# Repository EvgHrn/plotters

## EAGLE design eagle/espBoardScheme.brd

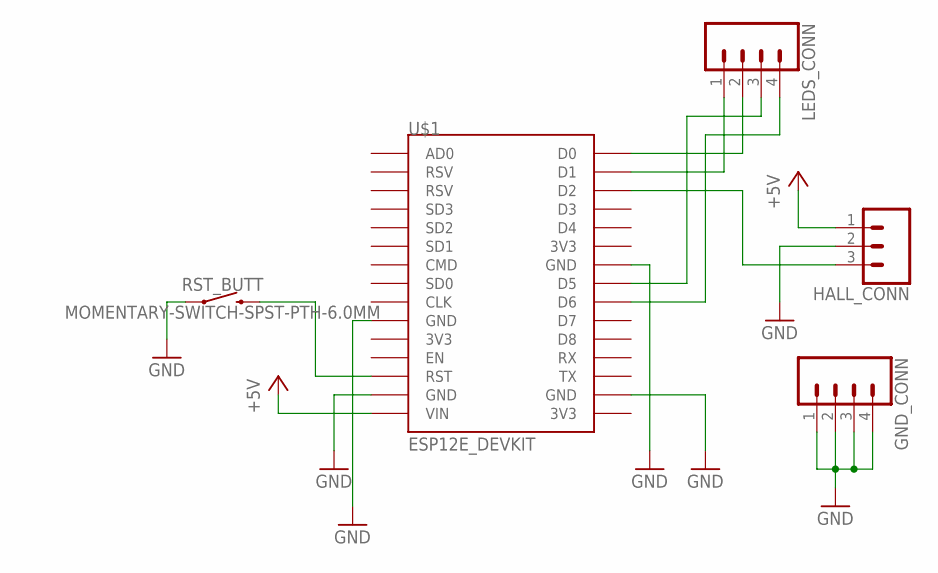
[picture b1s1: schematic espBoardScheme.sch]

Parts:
GND_CONN: CONN_04; 1X04
HALL_CONN: CONN_03; 1X03
LEDS_CONN: CONN_04; 1X04
RST_BUTT: MOMENTARY-SWITCH-SPST-PTH-6.0MM; TACTILE_SWITCH_PTH_6.0MM
U$1: ESP12E_DEVKIT

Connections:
+5V: HALL_CONN.1, U$1.VIN
GND: GND_CONN.1, GND_CONN.2, GND_CONN.3, GND_CONN.4, HALL_CONN.2, RST_BUTT.1, U$1.GND@0 (GND), U$1.GND@1 (GND), U$1.GND@2 (GND), U$1.GND@3 (GND)
unnamed: HALL_CONN.3, U$1.D2
unnamed: RST_BUTT.3 (2), U$1.RST
unnamed: LEDS_CONN.2, U$1.D0
unnamed: LEDS_CONN.1, U$1.D1
unnamed: LEDS_CONN.3, U$1.D5
unnamed: LEDS_CONN.4, U$1.D6

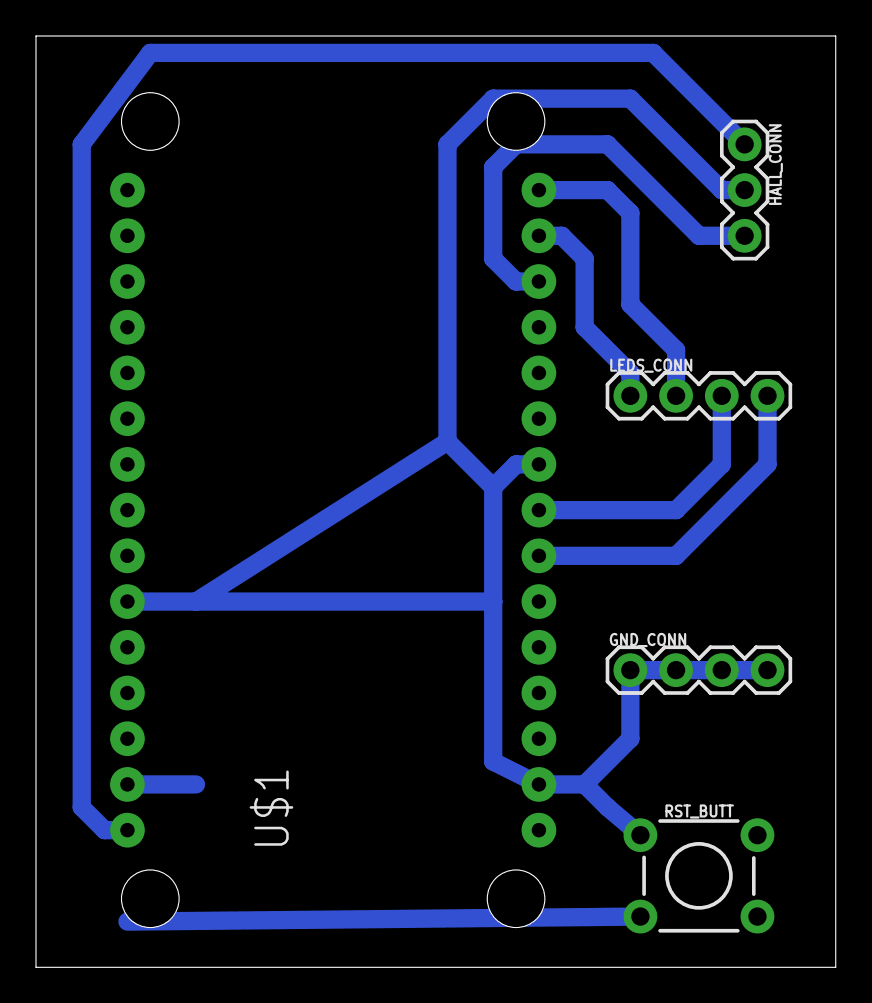
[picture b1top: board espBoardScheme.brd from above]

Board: 2 copper layers, 44.4 x 51.7 mm, 5 parts (0 on the bottom side), 8 nets.

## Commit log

2017-03-27 Init
2017-03-27 Add slim/pdo package
2017-03-27 Install slim/twig-view package
2017-03-27 Register twig on container
2017-03-27 Add first main root
2017-03-28 Some frontend
2017-03-28 Add simple google chart
2017-03-28 Add period select to form
2017-03-28 Add getting data for chart from json
2017-03-29 Add simple route for post
2017-03-29 Add db class skeleton
2017-03-29 Add saving GET data to database
2017-03-29 Edit .htaccess
2017-03-29 Start function to get data from db
2017-03-29 Add pwd fo db access
2017-03-30 dfsdf
2017-03-30 Add carbon package
2017-03-30 Start create DatesWorker
2017-03-31 Contin with DatesWorker
2017-03-31 Db getData sum meters for any period
2017-03-31 Add parcelWeeks to DatesWorker
2017-03-31 Add test for parcelDays
2017-03-31 Start add test for ParcelWeeks
2017-04-01 Fix bug in parcelDays
2017-04-01 Add testParcelMonths
2017-04-01 Add parcelMonths
2017-04-01 Add comments to parcelMonths
2017-04-01 Add testParcelYears
2017-04-01 Add parcelYears
2017-04-01 Add doc blocks to DatesWorker's methods
2017-04-01 Add doc blocks to Db class methods
2017-04-01 Make css and js local
2017-04-01 Fix some bugs
2017-04-01 Finish chart
2017-04-01 Add data.json for chart to gitignore
2017-04-01 Fix bug with time from form
2017-04-01 Add cookies for form
2017-04-05 Rename Db.php
2017-04-05 Rename DatesWorker.php
2017-04-05 Add try catch for writig to data.json file
2017-04-05 Fix bug in try catche block
2017-04-05 Add logging of /post data route
2017-04-05 Add arduino sketch
2017-04-06 Add logs page
2017-04-06 Fix bug in arduino sketch
2017-04-18 Change w5100 to esp8622
2017-04-25 Fix arduino sketch bug
2017-06-05 Getting time from ntp server
2017-06-05 Add error indication functions
2017-06-05 Change server address and ntp server
2017-06-06 Change wiriErr pin
2017-07-28 Added several ntp servers
2017-07-28 Add eagle project
2017-09-01 Added saving new speed field to db
2017-09-01 Send meters from post route to saveData method
2017-09-01 Send speed=0 from post route to saveData method
2017-09-01 Added calculating real speed
2017-09-01 Added some var_dump
2017-09-01 Conver meters to float in speed calculating
2017-10-06 Add print_logs route

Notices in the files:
parts and their libraries:
SparkFun-Connectors: Licensing: Creative Commons ShareAlike 4.0 International - https://creativecommons.org/licenses/by-sa/4.0
